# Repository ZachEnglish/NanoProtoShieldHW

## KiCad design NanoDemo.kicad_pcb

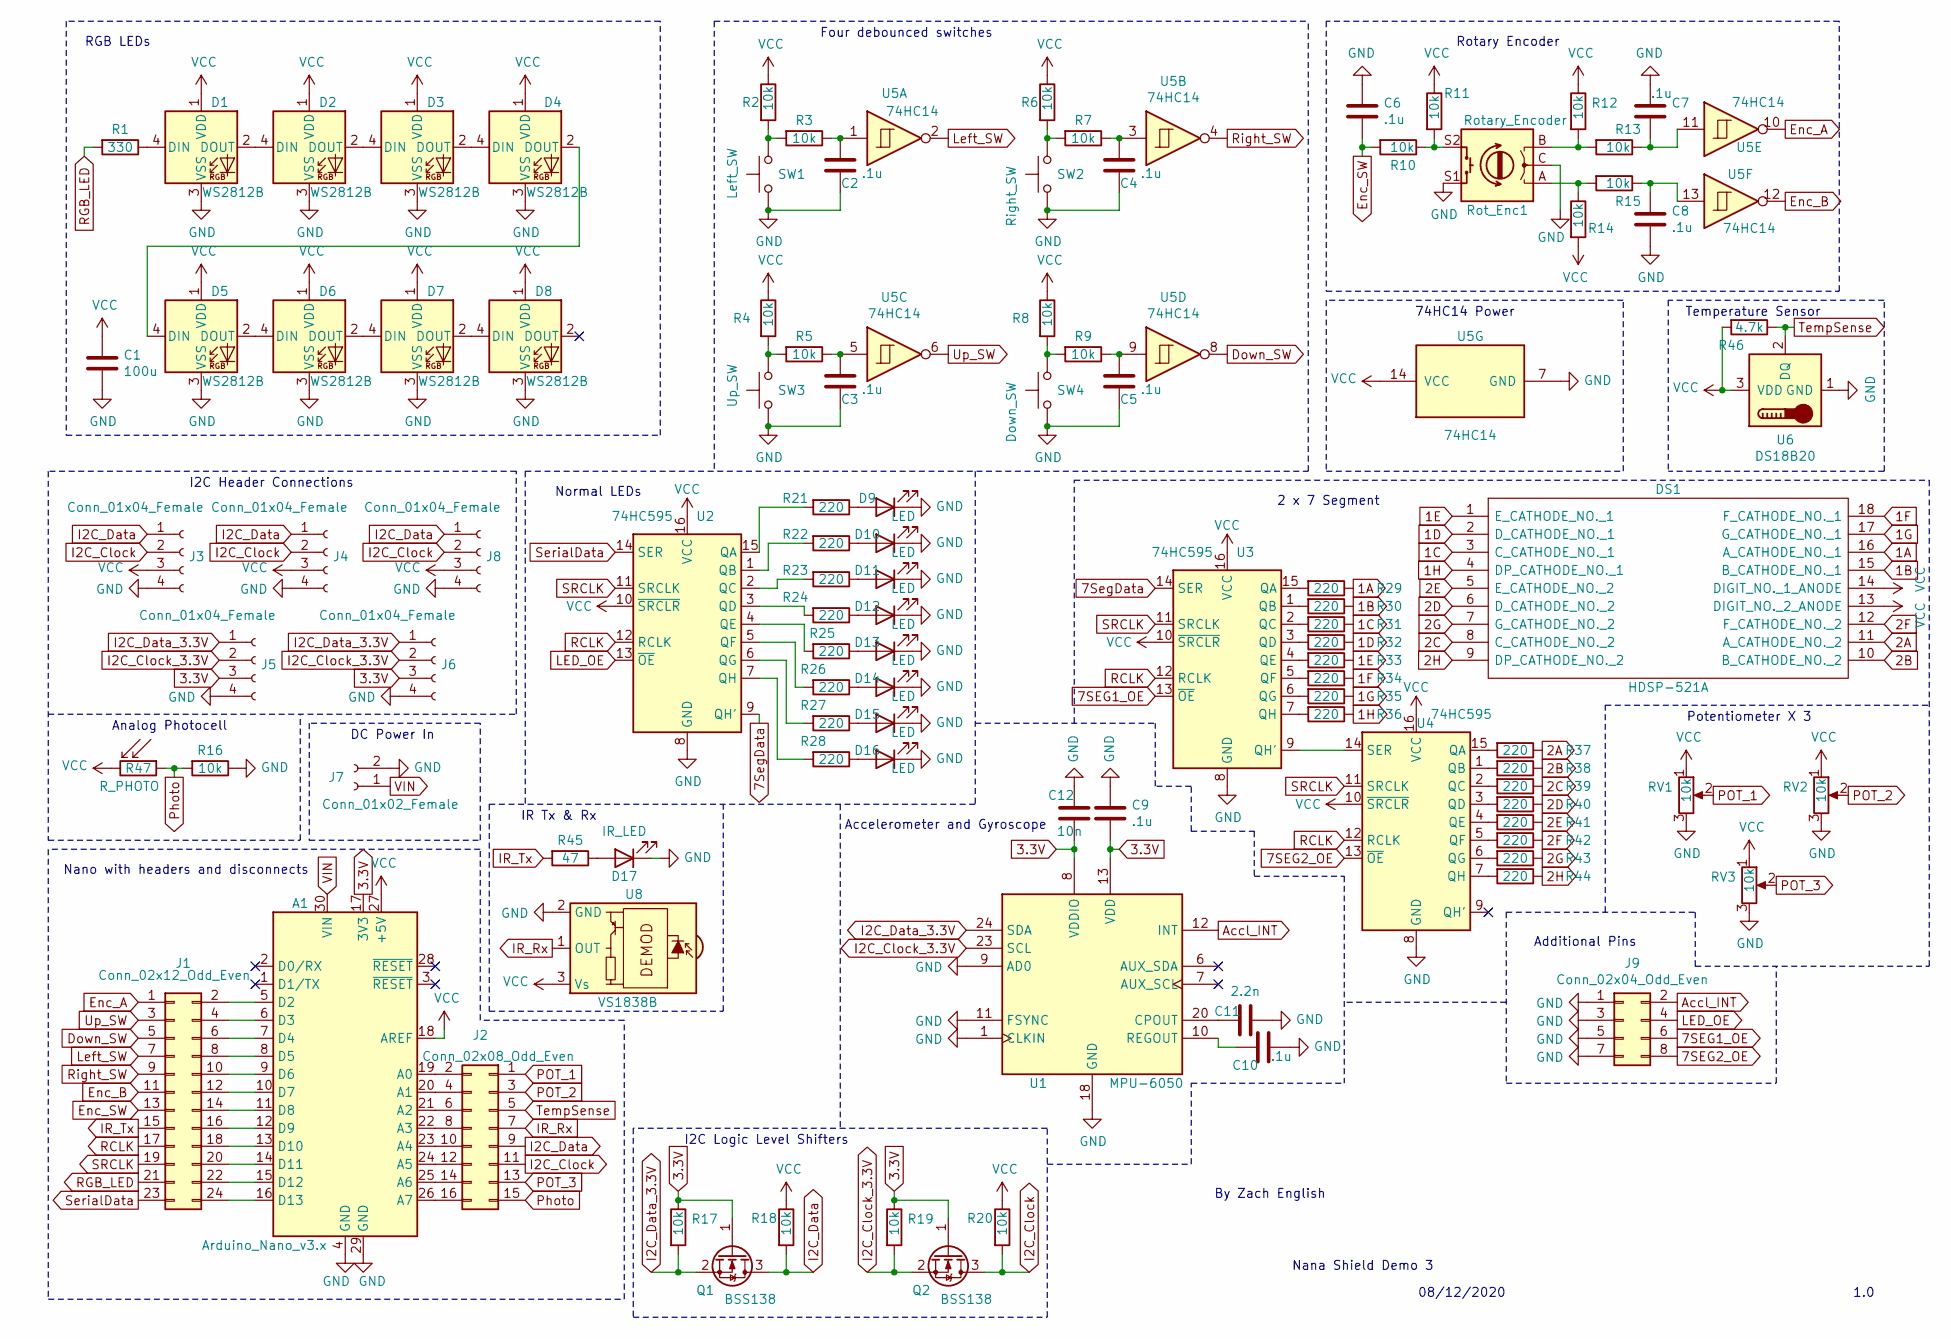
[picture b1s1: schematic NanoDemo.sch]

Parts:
A1: Arduino_Nano_v3.x; Arduino_Nano
C1: 100u; C_1206_3216Metric
C2, C3, C4, C5, C6, C7, C8, C9, C10: .1u; C_1206_3216Metric
C11: 2.2n; C_1206_3216Metric
C12: 10n; C_1206_3216Metric
D1, D2, D3, D4, D5, D6, D7, D8: WS2812B; LED_WS2812B_PLCC4_5.0x5.0mm_P3.2mm
D9, D10, D11, D12, D13, D14, D15, D16: LED; LED_D5.0mm
D17: IR_LED; LED_D5.0mm
DS1: HDSP-521A; DA56-11CGKWA; Mouser Part Number 630-HDSP-521A
J1: Conn_02x12_Odd_Even; PinHeader_2x12_P2.54mm_Vertical
J2: Conn_02x08_Odd_Even; PinHeader_2x08_P2.54mm_Vertical
J3, J4, J5, J6, J8: Conn_01x04_Female; PinSocket_1x04_P2.54mm_Vertical
J7: Conn_01x02_Female; PinSocket_1x02_P2.54mm_Vertical
J9: Conn_02x04_Odd_Even; PinHeader_2x04_P2.54mm_Vertical
Q1, Q2: BSS138; SOT-23
R1: 330; R_1206_3216Metric
R2, R3, R4, R5, R6, R7, R8, R9, R10, R11, R12, R13, R14, R15, R16, R17, R18, R19, R20: 10k; R_1206_3216Metric
R21, R22, R23, R24, R25, R26, R27, R28, R29, R30, R31, R32, R33, R34, R35, R36, R37, R38, R39, R40, R41, R42, R43, R44: 220; R_1206_3216Metric
R45: 47; R_1206_3216Metric
R46: 4.7k; R_1206_3216Metric
R47: R_PHOTO; R_LDR_4.9x4.2mm_P2.54mm_Vertical
RV1, RV2, RV3: 10k; Potentiometer_Runtron_RM-065_Vertical
Rot_Enc1: Rotary_Encoder; RotaryEncoder_Alps_EC11E_Vertical_H20mm
SW1: Left_SW; SW_PUSH_6mm
SW2: Right_SW; SW_PUSH_6mm
SW3: Up_SW; SW_PUSH_6mm
SW4: Down_SW; SW_PUSH_6mm
U1: MPU-6050; InvenSense_QFN-24_4x4mm_P0.5mm
U2, U3, U4: 74HC595; DIP-16_W7.62mm
U5: 74HC14; DIP-14_W7.62mm
U6: DS18B20; TO-92_Inline
U8: VS1838B; Vishay_MINICAST-3Pin

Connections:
1A: DS1.16 (A_CATHODE_NO._1), R29.1
1B: DS1.15 (B_CATHODE_NO._1), R30.1
1C: DS1.3 (C_CATHODE_NO._1), R31.1
1D: DS1.2 (D_CATHODE_NO._1), R32.1
1E: DS1.1 (E_CATHODE_NO._1), R33.1
1F: DS1.18 (F_CATHODE_NO._1), R34.1
1G: DS1.17 (G_CATHODE_NO._1), R35.1
1H: DS1.4 (DP_CATHODE_NO._1), R36.1
2A: DS1.11 (A_CATHODE_NO._2), R37.1
2B: DS1.10 (B_CATHODE_NO._2), R38.1
2C: DS1.8 (C_CATHODE_NO._2), R39.1
2D: DS1.6 (D_CATHODE_NO._2), R40.1
2E: DS1.5 (E_CATHODE_NO._2), R41.1
2F: DS1.12 (F_CATHODE_NO._2), R42.1
2G: DS1.7 (G_CATHODE_NO._2), R43.1
2H: DS1.9 (DP_CATHODE_NO._2), R44.1
3.3V: A1.17 (3V3), C9.2, C12.2, J5.3, J6.3, Q1.1 (G), Q2.1 (G), R17.1, R19.1, U1.8 (VDDIO), U1.13 (VDD)
7SEG1_OE: J9.6, U3.13 (~OE)
7SEG2_OE: J9.8, U4.13 (~OE)
7SegData: U2.9 (QH'), U3.14 (SER)
Accl_INT: J9.2, U1.12 (INT)
Down_SW: J1.5, U5.8
Enc_A: J1.1, U5.10
Enc_B: J1.11, U5.12
Enc_SW: C6.2, J1.13, R10.2
GND: A1.4 (GND), A1.29 (GND), C1.2, C2.2, C3.2, C4.2, C5.2, C6.1, C7.1, C8.2, C9.1, C10.2, C11.1, C12.1, D1.3 (VSS), D2.3 (VSS), D3.3 (VSS), D4.3 (VSS), D5.3 (VSS), D6.3 (VSS), D7.3 (VSS), D8.3 (VSS), D9.1 (K), D10.1 (K), D11.1 (K), D12.1 (K), D13.1 (K), D14.1 (K), D15.1 (K), D16.1 (K), D17.1 (K), J3.4, J4.4, J5.4, J6.4, J7.2, J8.4, J9.1, J9.3, J9.5, J9.7, R16.1, RV1.3, RV2.3, RV3.3, Rot_Enc1.C, Rot_Enc1.S1, SW1.1, SW2.1, SW3.1, SW4.1, U1.1 (CLKIN), U1.9 (AD0), U1.11 (FSYNC), U1.18 (GND), U2.8 (GND), U3.8 (GND), U4.8 (GND), U5.7 (GND), U6.1 (GND), U8.2 (GND); also elsewhere on the board
I2C_Clock: J2.11, J3.2, J4.2, J8.2, Q2.3 (D), R20.2; also elsewhere on the board
I2C_Clock_3.3V: J5.2, J6.2, Q2.2 (S), R19.2, U1.23 (SCL)
I2C_Data: J2.9, J3.1, J4.1, J8.1, Q1.3 (D), R18.2; also elsewhere on the board
I2C_Data_3.3V: J5.1, J6.1, Q1.2 (S), R17.2, U1.24 (SDA)
IR_Rx: J2.7, U8.1 (OUT)
IR_Tx: J1.15, R45.2
LED_OE: J9.4, U2.13 (~OE)
Left_SW: J1.7, U5.2
unnamed: A1.5 (D2), J1.2
unnamed: A1.6 (D3), J1.4
unnamed: A1.7 (D4), J1.6
unnamed: A1.8 (D5), J1.8
unnamed: A1.9 (D6), J1.10
unnamed: A1.10 (D7), J1.12
unnamed: A1.11 (D8), J1.14
unnamed: A1.12 (D9), J1.16
unnamed: A1.13 (D10), J1.18
unnamed: A1.14 (D11), J1.20
unnamed: A1.15 (D12), J1.22
unnamed: A1.16 (D13), J1.24
unnamed: A1.19 (A0), J2.2
unnamed: A1.20 (A1), J2.4
unnamed: A1.21 (A2), J2.6
unnamed: A1.22 (A3), J2.8
unnamed: A1.23 (A4), J2.10
unnamed: A1.24 (A5), J2.12
unnamed: A1.25 (A6), J2.14
unnamed: A1.26 (A7), J2.16
unnamed: C2.1, R3.1, U5.1
unnamed: C3.1, R5.1, U5.5
unnamed: C4.1, R7.1, U5.3
unnamed: C5.1, R9.1, U5.9
unnamed: C7.2, R13.1, U5.11
unnamed: C8.1, R15.1, U5.13
unnamed: C10.1, U1.10 (REGOUT)
unnamed: C11.2, U1.20 (CPOUT)
unnamed: D1.2 (DOUT), D2.4 (DIN)
unnamed: D1.4 (DIN), R1.1
unnamed: D2.2 (DOUT), D3.4 (DIN)
unnamed: D3.2 (DOUT), D4.4 (DIN)
unnamed: D4.2 (DOUT), D5.4 (DIN)
unnamed: D5.2 (DOUT), D6.4 (DIN)
unnamed: D6.2 (DOUT), D7.4 (DIN)
unnamed: D7.2 (DOUT), D8.4 (DIN)
unnamed: D9.2 (A), R21.1
unnamed: D10.2 (A), R22.1
unnamed: D11.2 (A), R23.1
unnamed: D12.2 (A), R24.1
unnamed: D13.2 (A), R25.1
unnamed: D14.2 (A), R26.1
unnamed: D15.2 (A), R27.1
unnamed: D16.2 (A), R28.1
unnamed: D17.2 (A), R45.1
unnamed: R2.2, R3.2, SW1.2
unnamed: R4.2, R5.2, SW3.2
unnamed: R6.2, R7.2, SW2.2
unnamed: R8.2, R9.2, SW4.2
unnamed: R10.1, R11.2, Rot_Enc1.S2
unnamed: R12.2, R13.2, Rot_Enc1.B
unnamed: R14.1, R15.2, Rot_Enc1.A
unnamed: R21.2, U2.15 (QA)
unnamed: R22.2, U2.1 (QB)
unnamed: R23.2, U2.2 (QC)
unnamed: R24.2, U2.3 (QD)
unnamed: R25.2, U2.4 (QE)
unnamed: R26.2, U2.5 (QF)
unnamed: R27.2, U2.6 (QG)
unnamed: R28.2, U2.7 (QH)
unnamed: R29.2, U3.15 (QA)
unnamed: R30.2, U3.1 (QB)
unnamed: R31.2, U3.2 (QC)
unnamed: R32.2, U3.3 (QD)
unnamed: R33.2, U3.4 (QE)
unnamed: R34.2, U3.5 (QF)
unnamed: R35.2, U3.6 (QG)
unnamed: R36.2, U3.7 (QH)
unnamed: R37.2, U4.15 (QA)
unnamed: R38.2, U4.1 (QB)
unnamed: R39.2, U4.2 (QC)
unnamed: R40.2, U4.3 (QD)
unnamed: R41.2, U4.4 (QE)
unnamed: R42.2, U4.5 (QF)
unnamed: R43.2, U4.6 (QG)
unnamed: R44.2, U4.7 (QH)
unnamed: U3.9 (QH'), U4.14 (SER)
POT_1: J2.1, RV1.2
POT_2: J2.3, RV2.2
POT_3: J2.13, RV3.2
Photo: J2.15, R16.2, R47.1
RCLK: J1.17, U2.12 (RCLK), U3.12 (RCLK), U4.12 (RCLK)
RGB_LED: J1.21, R1.2
Right_SW: J1.9, U5.4
SRCLK: J1.19, U2.11 (SRCLK), U3.11 (SRCLK), U4.11 (SRCLK)
SerialData: J1.23, U2.14 (SER)
TempSense: J2.5, R46.1, U6.2 (DQ)
Up_SW: J1.3, U5.6
VCC: A1.18 (AREF), A1.27 (+5V), C1.1, D1.1 (VDD), D2.1 (VDD), D3.1 (VDD), D4.1 (VDD), D5.1 (VDD), D6.1 (VDD), D7.1 (VDD), D8.1 (VDD), DS1.13 (DIGIT_NO._2_ANODE), DS1.14 (DIGIT_NO._1_ANODE), J3.3, J4.3, J8.3, R2.1, R4.1, R6.1, R8.1, R11.1, R12.1, R14.2, R18.1, R20.1, R46.2, R47.2, RV1.1, RV2.1, RV3.1, U2.10 (~SRCLR), U2.16 (VCC), U3.10 (~SRCLR), U3.16 (VCC), U4.10 (~SRCLR), U4.16 (VCC), U5.14 (VCC), U6.3 (VDD), U8.3 (Vs); also elsewhere on the board
VIN: A1.30 (VIN), J7.1

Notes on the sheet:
RGB LEDs
Four debounced switches
Rotary Encoder
74HC14 Power
2 x 7 Segment
Potentiometer X 3
I2C Header Connections
Nano with headers and disconnects
Normal LEDs
Analog Photocell
Temperature Sensor
IR Tx & Rx
Nana Shield Demo 3
1.0
08/12/2020
By Zach English
DC Power In
I2C Logic Level Shifters
Accelerometer and Gyroscope
Additional Pins

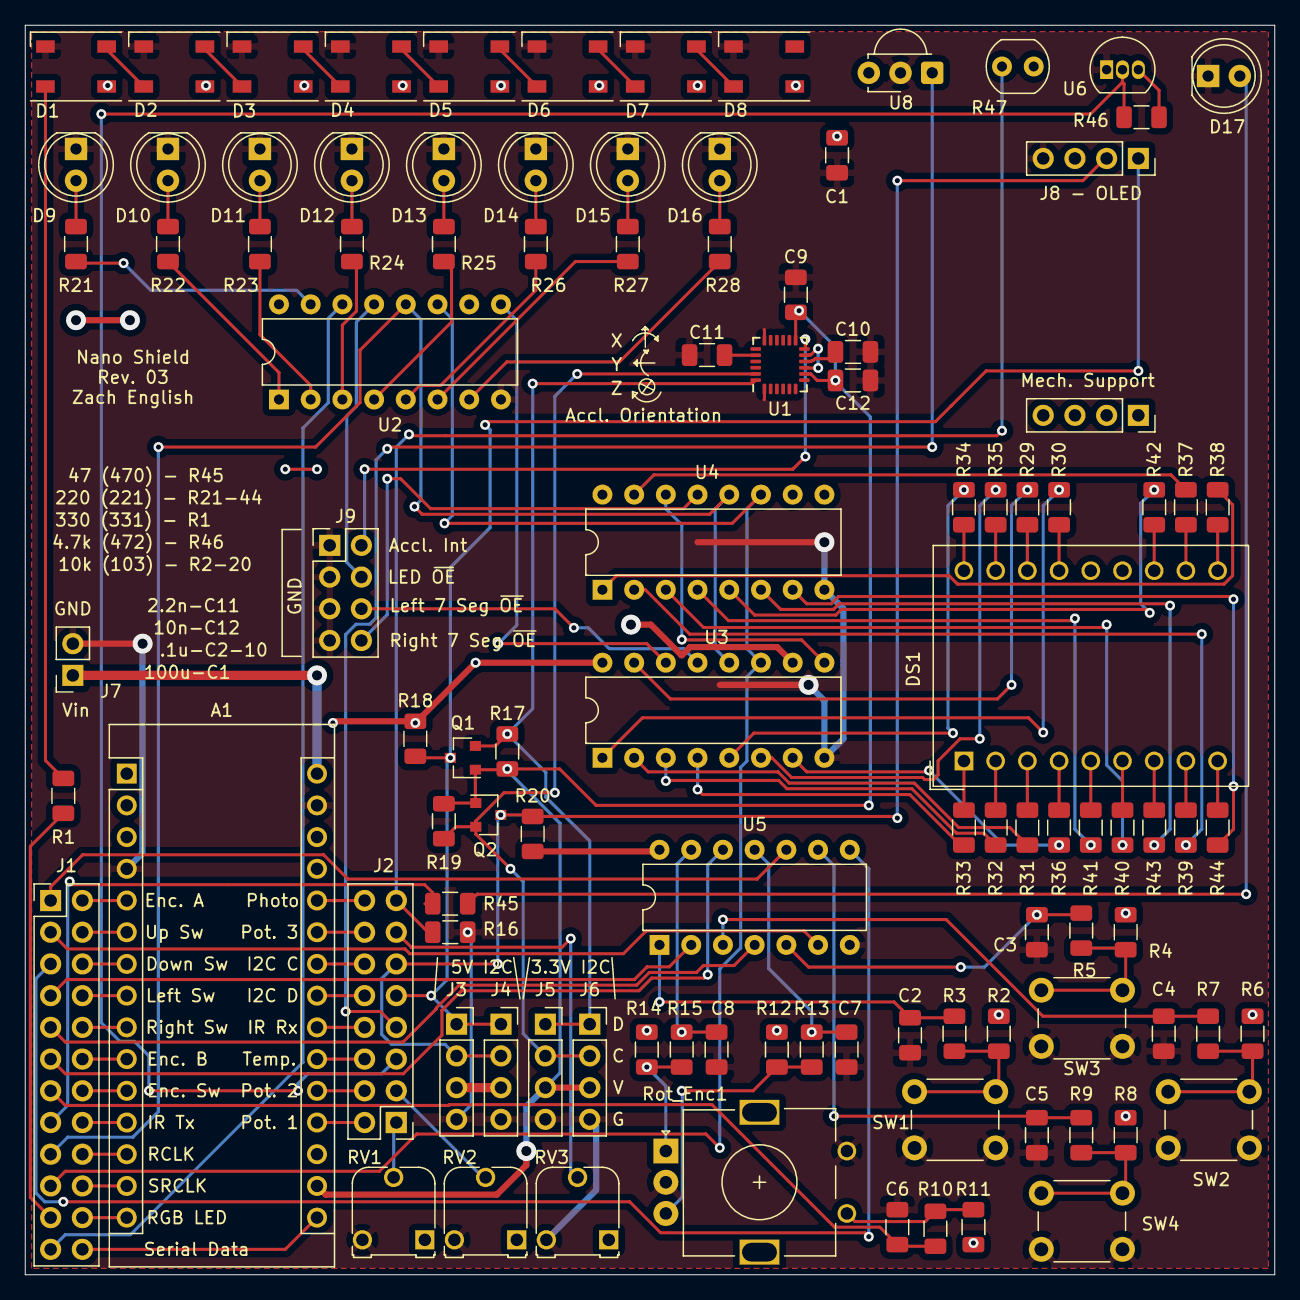
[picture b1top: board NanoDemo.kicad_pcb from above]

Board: 2 copper layers, 100.1 x 100.1 mm, 106 parts (0 on the bottom side), 124 nets.

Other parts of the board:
Accl. Orientation: XYZ
J8 - OLED: Conn_01x04_Female; PinSocket_1x04_P2.54mm_Vertical
Mech. Support: PinSocket_1x04_P2.54mm_Vertical

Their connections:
GND: J8 - OLED.4; also elsewhere on the board
I2C_Clock: J8 - OLED.2; also elsewhere on the board
I2C_Data: J8 - OLED.1; also elsewhere on the board
VCC: J8 - OLED.3; also elsewhere on the board

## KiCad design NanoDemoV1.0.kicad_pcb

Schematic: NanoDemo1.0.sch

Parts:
A1: Arduino_Nano_v2.x; Arduino_Nano
C1, C2, C3, C4, C5, C6, C7: 0.1uF; C_Disc_D3.0mm_W2.0mm_P2.50mm
D1, D2, D3, D4, D5, D6, D7, D8: Inolux_IN-PI554FCH; LED_Inolux_IN-PI554FCH_PLCC4_5.0x5.0mm_P3.2mm
D9, D10, D11, D12, D13, D14, D15, D16: LED; LED_D3.0mm
DS1: HDSP-521A; DA56-11CGKWA; Mouser Part Number 630-HDSP-521A
J1, J2, J3, J4, J5: Conn_01x04_Female; PinHeader_1x04_P2.54mm_Vertical
R1, R2, R3, R4, R5, R6, R7, R8, R9, R10, R11, R20, R21, R22, R23, R24, R25, R26, R27: 10k; R_Axial_DIN0207_L6.3mm_D2.5mm_P10.16mm_Horizontal
R12, R13, R14, R15, R16, R17, R18, R19, R28, R29, R30, R31, R32, R33, R34, R35, R36, R37, R38, R39, R40, R41, R42, R43: 220; R_Axial_DIN0207_L6.3mm_D2.5mm_P10.16mm_Horizontal
RV1, RV2, RV3: R_POT_TRIM_US; Potentiometer_Runtron_RM-065_Vertical
SW1: SW - Left; SW_PUSH_6mm
SW2: SW - Right; SW_PUSH_6mm
SW3: SW - Up; SW_PUSH_6mm
SW4: Rotary_Encoder_Switch; RotaryEncoder_Alps_EC11E_Vertical_H20mm
SW5: SW - Down; SW_PUSH_6mm
U1: 74HC14; DIP-14_W7.62mm
U2, U4, U6: 74HC595; DIP-16_W7.62mm
U5: ULN2803A; DIP-18_W7.62mm

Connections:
7SegData: A1.16, U4.14 (SER)
GND: A1.4, A1.29, C1.2, C2.2, C3.2, C4.2, C5.2, C6.2, C7.2, D1.1, D2.1, D3.1, D4.1, D5.1, D6.1, D7.1, D8.1, J1.4, J2.4, J3.4, J4.4, J5.4, RV1.1, RV2.1, RV3.1, SW1.1, SW1.2, SW2.1, SW2.2, SW3.1, SW3.2, SW4.C, SW4.S1, SW5.1, SW5.2, U1.7 (GND), U2.8 (GND), U2.13 (~OE), U4.8 (GND), U4.13 (~OE), U5.9, U6.8 (GND), U6.13 (~OE)
I2C_Clock: A1.24, J1.3, J2.3, J3.3, J4.3, J5.2
I2C_Data: A1.23, J1.2, J2.2, J3.2, J4.2, J5.1
unnamed: A1.5, U1.12
unnamed: A1.6, U1.6
unnamed: A1.7, U1.4
unnamed: A1.8, U1.2
unnamed: A1.9, C3.1, R5.2, SW4.S2
unnamed: A1.10, U1.8
unnamed: A1.11, U1.10
unnamed: A1.14, U2.14 (SER)
unnamed: A1.15, D1.2
unnamed: A1.19, RV1.2
unnamed: A1.20, RV2.2
unnamed: A1.21, RV3.2
unnamed: C1.1, R2.2, U1.1
unnamed: C2.1, R4.2, U1.3
unnamed: C4.1, R7.2, U1.5
unnamed: C5.1, R8.2, SW4.B, U1.9
unnamed: C6.1, R10.2, SW4.A, U1.11
unnamed: C7.1, R11.2, U1.13
unnamed: D1.4, D2.2
unnamed: D2.4, D3.2
unnamed: D3.4, D4.2
unnamed: D4.4, D5.2
unnamed: D5.4, D6.2
unnamed: D6.4, D7.2
unnamed: D7.4, D8.2
unnamed: D9.1 (K), R19.2
unnamed: D10.1 (K), R12.2
unnamed: D11.1 (K), R13.2
unnamed: D12.1 (K), R14.2
unnamed: D13.1 (K), R15.2
unnamed: D14.1 (K), R16.2
unnamed: D15.1 (K), R17.2
unnamed: D16.1 (K), R18.2
unnamed: DS1.1 (E_CATHODE_NO._1), R32.1
unnamed: DS1.2 (D_CATHODE_NO._1), R31.1
unnamed: DS1.3 (C_CATHODE_NO._1), R30.1
unnamed: DS1.4 (DP_CATHODE_NO._1), R35.1
unnamed: DS1.5 (E_CATHODE_NO._2), R40.1
unnamed: DS1.6 (D_CATHODE_NO._2), R39.1
unnamed: DS1.7 (G_CATHODE_NO._2), R42.1
unnamed: DS1.8 (C_CATHODE_NO._2), R38.1
unnamed: DS1.9 (DP_CATHODE_NO._2), R43.1
unnamed: DS1.10 (B_CATHODE_NO._2), R37.1
unnamed: DS1.11 (A_CATHODE_NO._2), R36.1
unnamed: DS1.12 (F_CATHODE_NO._2), R41.1
unnamed: DS1.15 (B_CATHODE_NO._1), R29.1
unnamed: DS1.16 (A_CATHODE_NO._1), R28.1
unnamed: DS1.17 (G_CATHODE_NO._1), R34.1
unnamed: DS1.18 (F_CATHODE_NO._1), R33.1
unnamed: R1.2, R2.1, SW1.3, SW1.4
unnamed: R3.2, R4.1, SW2.3, SW2.4
unnamed: R6.2, R7.1, SW3.3, SW3.4
unnamed: R9.2, R11.1, SW5.3, SW5.4
unnamed: R12.1, U5.11
unnamed: R13.1, U5.12
unnamed: R14.1, U5.13
unnamed: R15.1, U5.14
unnamed: R16.1, U5.15
unnamed: R17.1, U5.16
unnamed: R18.1, U5.17
unnamed: R19.1, U5.18
unnamed: R20.1, U2.7 (QH)
unnamed: R20.2, U5.8
unnamed: R21.1, U2.6 (QG)
unnamed: R21.2, U5.7
unnamed: R22.1, U2.5 (QF)
unnamed: R22.2, U5.6
unnamed: R23.1, U2.4 (QE)
unnamed: R23.2, U5.5
unnamed: R24.1, U2.3 (QD)
unnamed: R24.2, U5.4
unnamed: R25.1, U2.2 (QC)
unnamed: R25.2, U5.3
unnamed: R26.1, U2.1 (QB)
unnamed: R26.2, U5.2
unnamed: R27.1, U2.15 (QA)
unnamed: R27.2, U5.1
unnamed: R28.2, U4.15 (QA)
unnamed: R29.2, U4.1 (QB)
unnamed: R30.2, U4.2 (QC)
unnamed: R31.2, U4.3 (QD)
unnamed: R32.2, U4.4 (QE)
unnamed: R33.2, U4.5 (QF)
unnamed: R34.2, U4.6 (QG)
unnamed: R35.2, U4.7 (QH)
unnamed: R36.2, U6.15 (QA)
unnamed: R37.2, U6.1 (QB)
unnamed: R38.2, U6.2 (QC)
unnamed: R39.2, U6.3 (QD)
unnamed: R40.2, U6.4 (QE)
unnamed: R41.2, U6.5 (QF)
unnamed: R42.2, U6.6 (QG)
unnamed: R43.2, U6.7 (QH)
RCLK: A1.12, U2.12 (RCLK), U4.12 (RCLK), U6.12 (RCLK)
SRCLK: A1.13, U2.11 (SRCLK), U4.11 (SRCLK), U6.11 (SRCLK)
ShiftR1OutR2In: U4.9 (QH'), U6.14 (SER)
VCC: A1.18, A1.27, D1.3, D2.3, D3.3, D4.3, D5.3, D6.3, D7.3, D8.3, D9.2 (A), D10.2 (A), D11.2 (A), D12.2 (A), D13.2 (A), D14.2 (A), D15.2 (A), D16.2 (A), DS1.13 (DIGIT_NO._2_ANODE), DS1.14 (DIGIT_NO._1_ANODE), J1.1, J2.1, J3.1, J4.1, J5.3, R1.1, R3.1, R5.1, R6.1, R8.1, R9.1, R10.1, RV1.3, RV2.3, RV3.3, U1.14 (VCC), U2.10 (~SRCLR), U2.16 (VCC), U4.10 (~SRCLR), U4.16 (VCC), U5.10, U6.10 (~SRCLR), U6.16 (VCC)

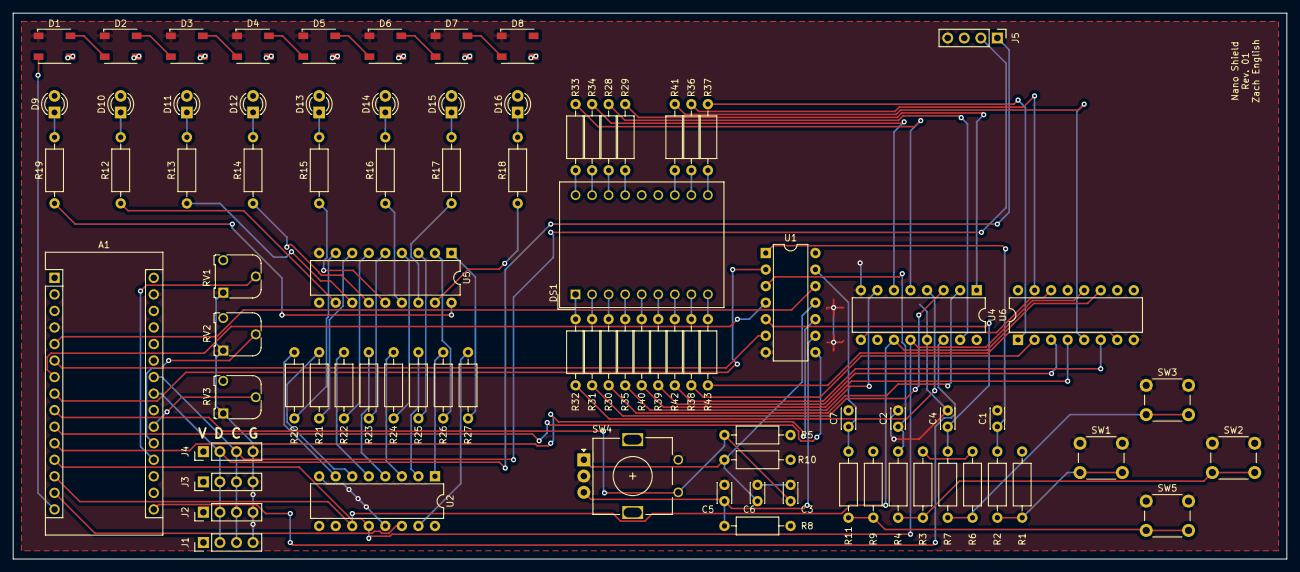
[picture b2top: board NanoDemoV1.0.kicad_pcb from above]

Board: 2 copper layers, 195.6 x 83.8 mm, 86 parts (0 on the bottom side), 101 nets.

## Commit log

2021-01-09 Initial git tracking. Project V3.0 already complete and assembled.
